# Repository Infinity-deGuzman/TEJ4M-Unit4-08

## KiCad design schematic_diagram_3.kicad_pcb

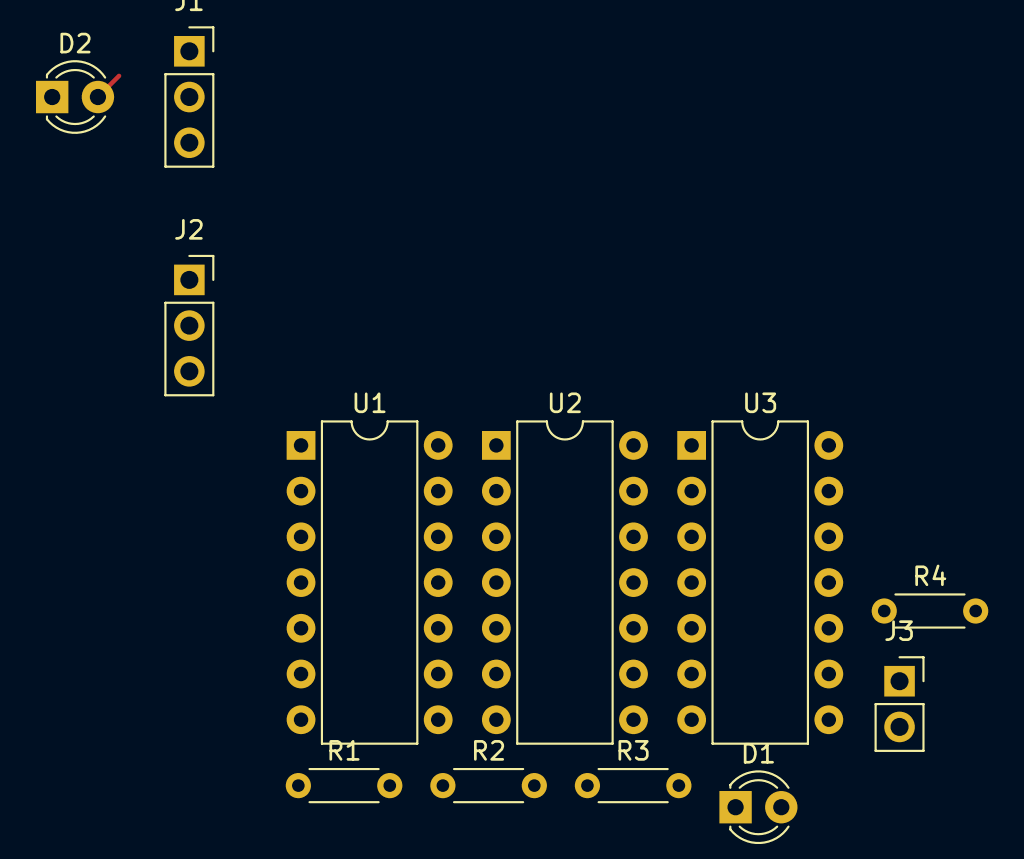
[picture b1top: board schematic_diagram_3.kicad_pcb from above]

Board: 2 copper layers, 12 parts (0 on the bottom side), 12 nets.

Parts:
D1, D2: LED; LED_D3.0mm
J1, J2: XLR3_Switched; PinSocket_1x03_P2.54mm_Vertical
J3: Conn_01x02_Female; PinSocket_1x02_P2.54mm_Vertical
R1, R2, R3, R4: R_US; R_Axial_DIN0204_L3.6mm_D1.6mm_P5.08mm_Horizontal
U1: 74LS04; DIP-14_W7.62mm
U2: 74AUC2G08; DIP-14_W7.62mm
U3: 74LVC2G02; DIP-14_W7.62mm

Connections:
GND: U2.4, U3.4
unnamed: D1.1, R3.2
unnamed: D1.2, U3.5, U3.7
unnamed: D2.1, R4.2
unnamed: D2.2, U3.2, U3.3
unnamed: J3.2, R3.1, R4.1
unnamed: R1.1, U1.1, U2.2
unnamed: R2.1, U2.1, U2.6
unnamed: U1.2, U2.5
unnamed: U2.3, U3.1
unnamed: U2.7, U3.6
VCC: U2.8, U3.8

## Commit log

2023-11-17 backup
